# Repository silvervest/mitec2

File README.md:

## Programming

I am using an el cheapo USB to FT232H UART adapter from AliExpress

### Pin connections

| JTAG | FTDI |
|------|------|
| TCK  | AD0  |
| TDI  | AD1  |
| TDO  | AD2  |
| TMS  | AD3  |
| VCC  | 3.3V |
| GND  | GND  |

### Steps

First we need to change the frequency line in the SVF file... The default 1MHz is too fast, so we're slowing it to 300KHz which seems to work fine.
```bash
$ sed -i "s/FREQUENCY 1E6 HZ/FREQUENCY 3E5 HZ/" mitec2.svf
```

Second we need to setup UrJTAG for the CPLD, but adding the xc9536xl_vq44 stepping to the configuration (you may need to change this file path depending on your install)
```bash
$ echo "0101    xc9536xl_vq44   5" | sudo tee -a /usr/local/share/urjtag/xilinx/xc9536xl/STEPPINGS
```

Finally, we can program
```bash
$ sudo jtag

UrJTAG 2021.03 #
Copyright (C) 2002, 2003 ETC s.r.o.
Copyright (C) 2007, 2008, 2009 Kolja Waschk and the respective authors

UrJTAG is free software, covered by the GNU General Public License, and you are
welcome to change it and/or distribute copies of it under certain conditions.
There is absolutely no warranty for UrJTAG.

warning: UrJTAG may damage your hardware!
Type "quit" to exit, "help" for help.

jtag> cable jtagkey vid=0x0403 pid=0x6014
Connected to libftdi driver.
jtag> detect
IR length: 8
Chain length: 1
Device Id: 01011001011000000010000010010011 (0x59602093)
  Manufacturer: Xilinx (0x093)
  Part(0):      xc9536xl (0x9602)
  Stepping:     5
  Filename:     /usr/local/share/urjtag/xilinx/xc9536xl/xc9536xl_vq44
jtag> svf hdl/mitec2.svf stop progress
detail: Parsing   5160/5163 ( 99%)detail: 
detail: Scanned device output matched expected TDO values.
jtag> 
```

If all went well, you will get the success message

`detail: Scanned device output matched expected TDO values.`

Your device is now programmed!

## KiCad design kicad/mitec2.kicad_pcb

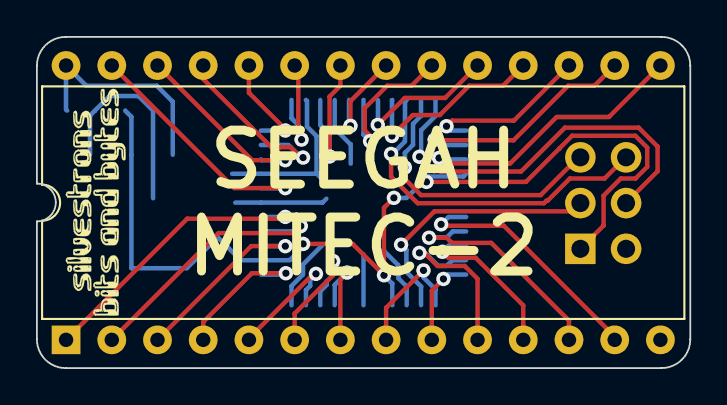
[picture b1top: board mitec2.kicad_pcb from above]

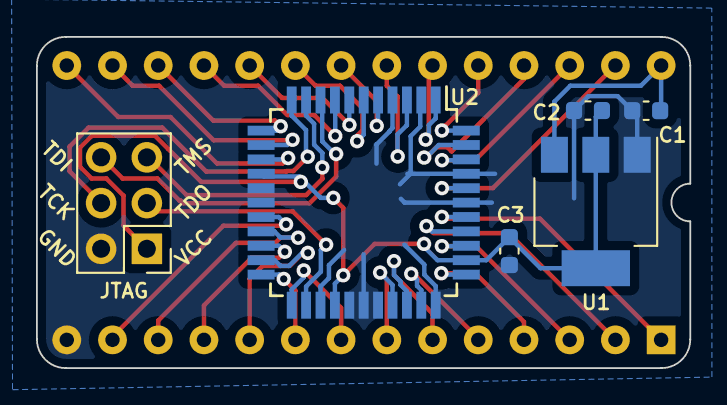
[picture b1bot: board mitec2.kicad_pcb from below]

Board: 2 copper layers, 36.3 x 18.4 mm, 7 parts (6 on the bottom side), 33 nets.

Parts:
C1, C2: 1uF; C_0603_1608Metric
C3: 100nF; C_0603_1608Metric
J1: MITEC2; DIP-28_W15.24mm_Socket
JTAG: JTAG; PinHeader_2x03_P2.54mm_Vertical
U1: AMS1117-3.3; SOT-223-3_TabPin2
U2: XC9536XL-10VQ44C; TQFP-44_10x10mm_P0.8mm

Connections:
+3V3: C2.1, C3.1, JTAG.1, U1.2 (VO), U2.15 (VCC), U2.26 (VCC), U2.35 (VCCIO)
+5V: C1.2, J1.28, U1.3 (VI)
/A6: J1.17, U2.12 (M13)
/A7: J1.18, U2.8 (M12)
/A14: J1.12, U2.19 (M17)
/A15: J1.13, U2.18 (M17)
/JTAG_TCK: JTAG.4, U2.11 (TCK)
/JTAG_TDI: JTAG.6, U2.9 (TDI)
/JTAG_TDO: JTAG.3, U2.24 (TDO)
/JTAG_TMS: JTAG.5, U2.10 (TMS)
/RAMA7: J1.19, U2.7 (M11)
/~CAS1: J1.23, U2.1 (M6)
/~CAS2: J1.24, U2.44 (I/O/GCK2)
/~CE89: J1.25, U2.43 (I/O/GCK1)
/~CEROM2: J1.16, U2.13 (M14)
/~CSR: J1.26, U2.42 (M4)
/~CSSRAM: J1.15, U2.14 (M15)
/~CSW: J1.27, U2.40 (M1)
/~IORQ: J1.6, U2.31 (M8)
/~IOR: J1.10, U2.21 (M16)
/~IOW: J1.11, U2.20 (M15)
/~MEMR: J1.8, U2.23 (M13)
/~MEMW: J1.9, U2.22 (M14)
/~MREQ: J1.2, U2.37 (M4)
/~MUX: J1.20, U2.6 (M10)
/~NMIN: J1.3, U2.36 (I/O/GTS1)
/~NMI: J1.1, U2.38 (M2)
/~RAS1: J1.21, U2.5 (M9)
/~RAS2: J1.22, U2.3 (M8)
/~RD: J1.4, U2.34 (I/O/GTS2)
/~RFSH: J1.7, U2.30 (M9)
/~WR: J1.5, U2.32 (M7)
GND: C1.1, C2.2, C3.2, J1.14, JTAG.2, U1.1 (GND), U2.2 (I/O/GCK3), U2.4 (GND), U2.16 (M16), U2.17 (GND), U2.25 (GND), U2.27 (M12), U2.28 (M11), U2.29 (M10), U2.33 (I/O/GSR), U2.39 (M1), U2.41 (M2)

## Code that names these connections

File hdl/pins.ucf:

NET "NMIN" LOC = "P36";
NET "RD" LOC = "P34";
NET "WR" LOC = "P32";
NET "MREQ" LOC = "P37";
NET "IORQ" LOC = "P31";
NET "RFSH" LOC = "P30";
NET "RAMA7" LOC = "P7";
NET "A6" LOC = "P12";
NET "A7" LOC = "P8";
NET "A14" LOC = "P19";
NET "A15" LOC = "P18";
NET "NMI" LOC = "P38";
NET "IOR" LOC = "P21";
NET "IOW" LOC = "P20";
NET "MEMR" LOC = "P23";
NET "MEMW" LOC = "P22";
NET "CSR" LOC = "P42";
NET "CSW" LOC = "P40";
NET "CE89" LOC = "P43";
NET "CSSRAM" LOC = "P14";
NET "CEROM2" LOC = "P13";
NET "CAS1" LOC = "P1";
NET "RAS1" LOC = "P5";
NET "CAS2" LOC = "P44";
NET "RAS2" LOC = "P3";
NET "MUX" LOC = "P6";

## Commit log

2022-11-19 working update for cart dram!
2022-11-20 clean up equations, lots of comments
2022-11-20 debouncing NMI
2022-12-02 adding license
